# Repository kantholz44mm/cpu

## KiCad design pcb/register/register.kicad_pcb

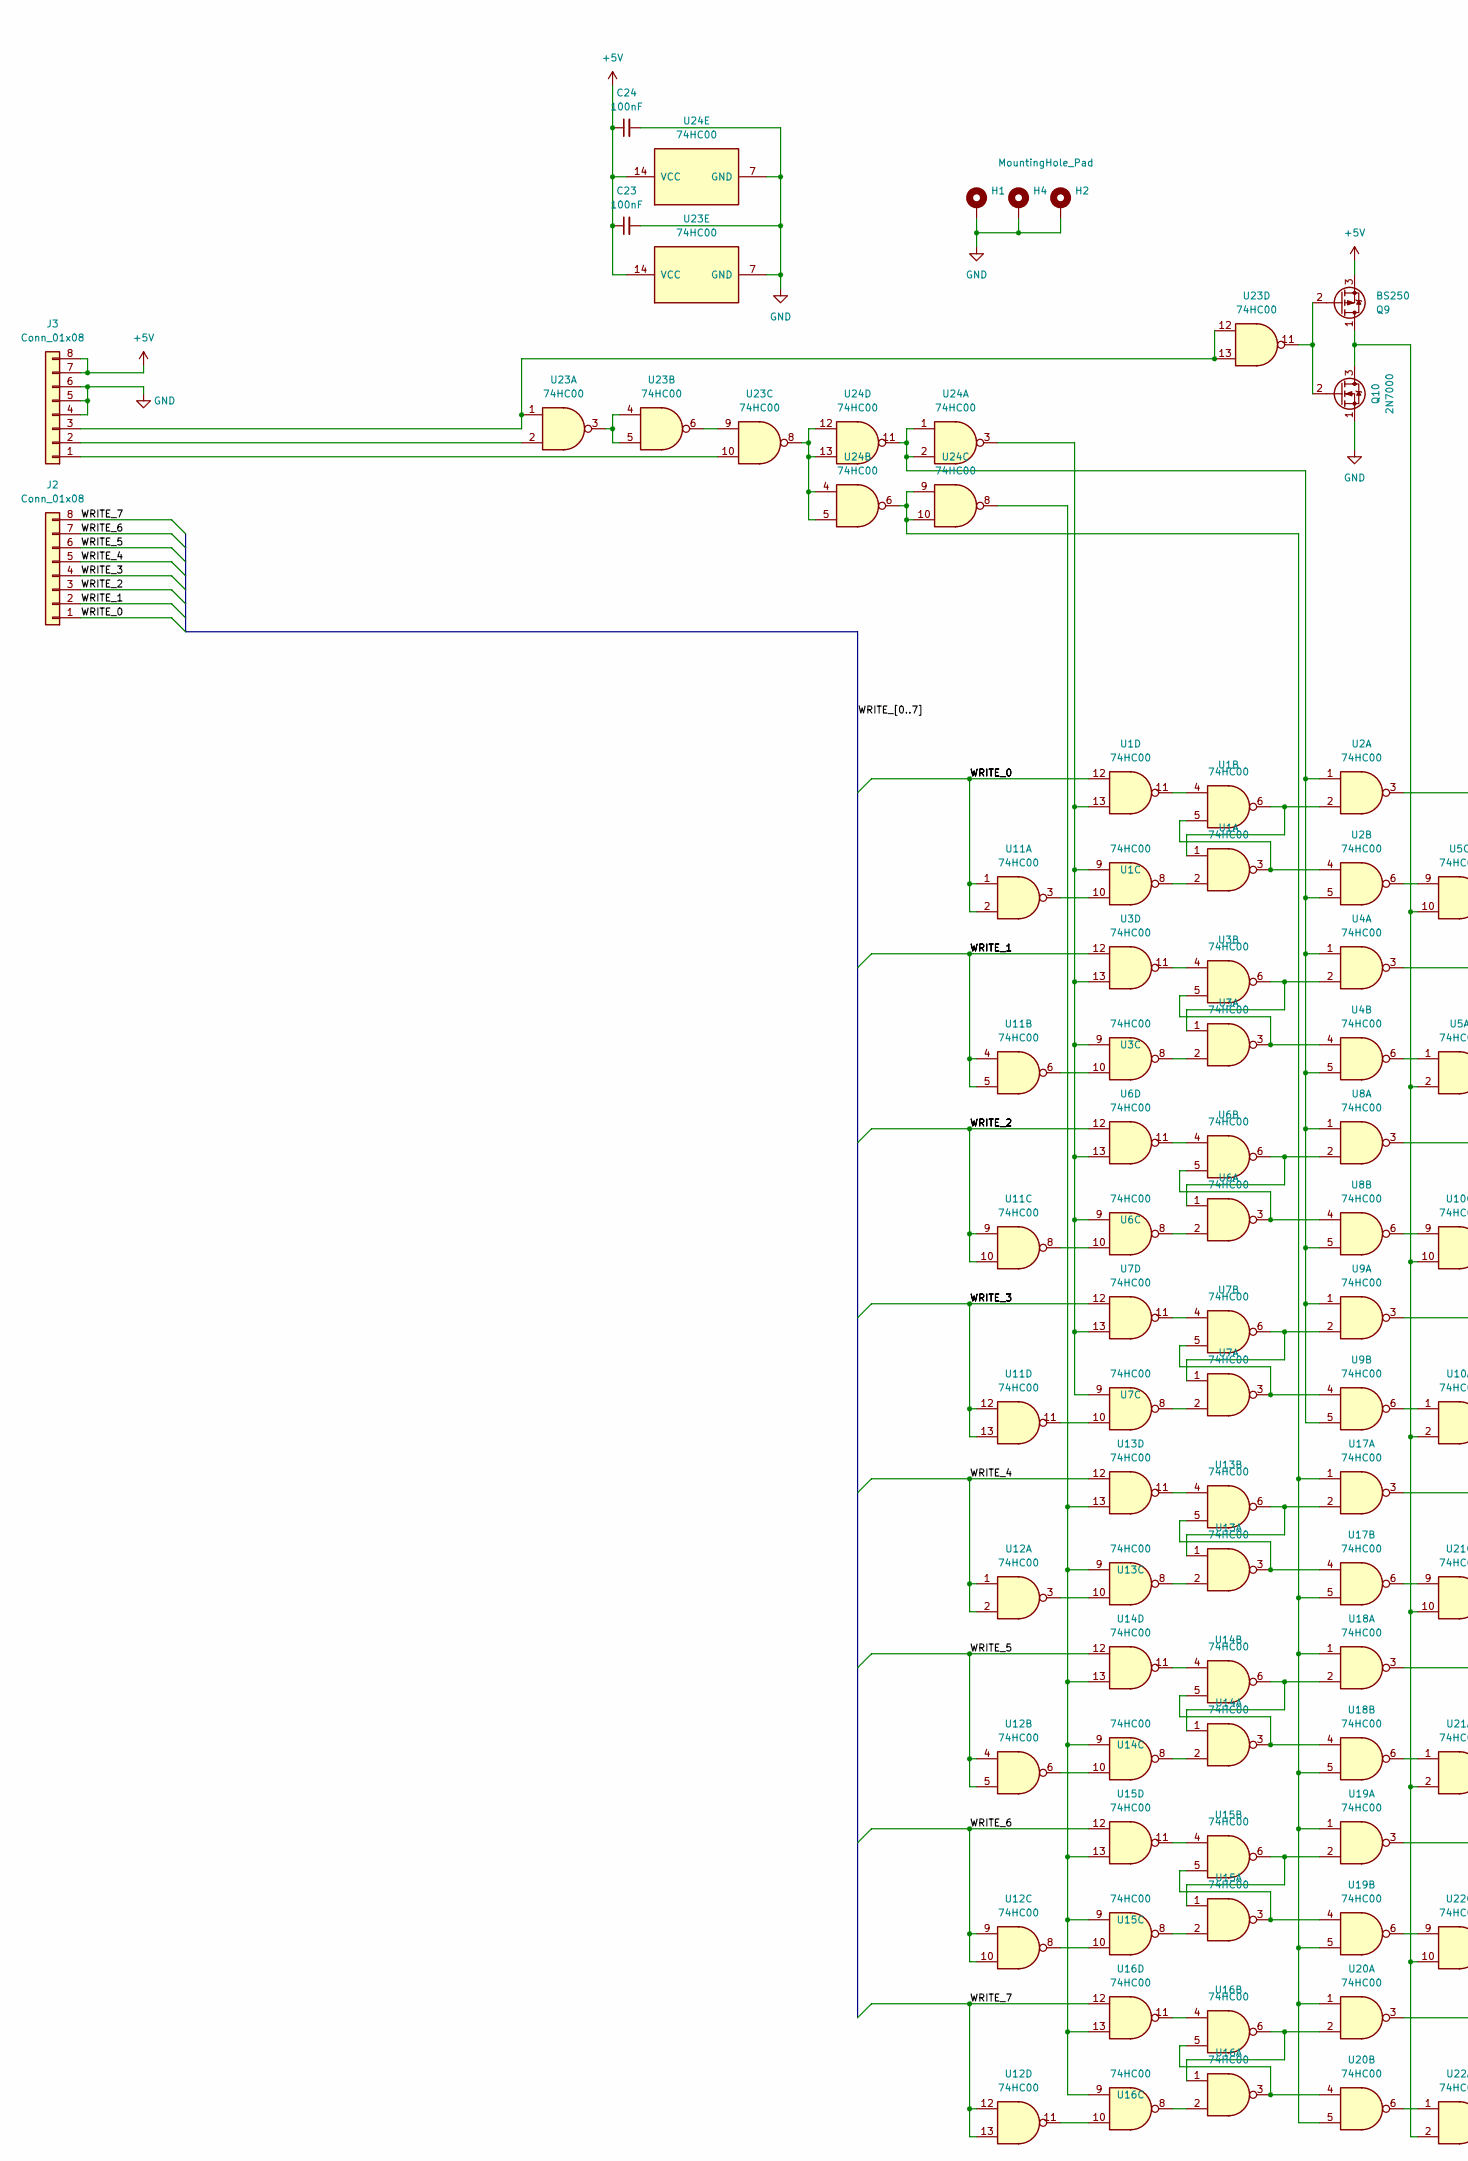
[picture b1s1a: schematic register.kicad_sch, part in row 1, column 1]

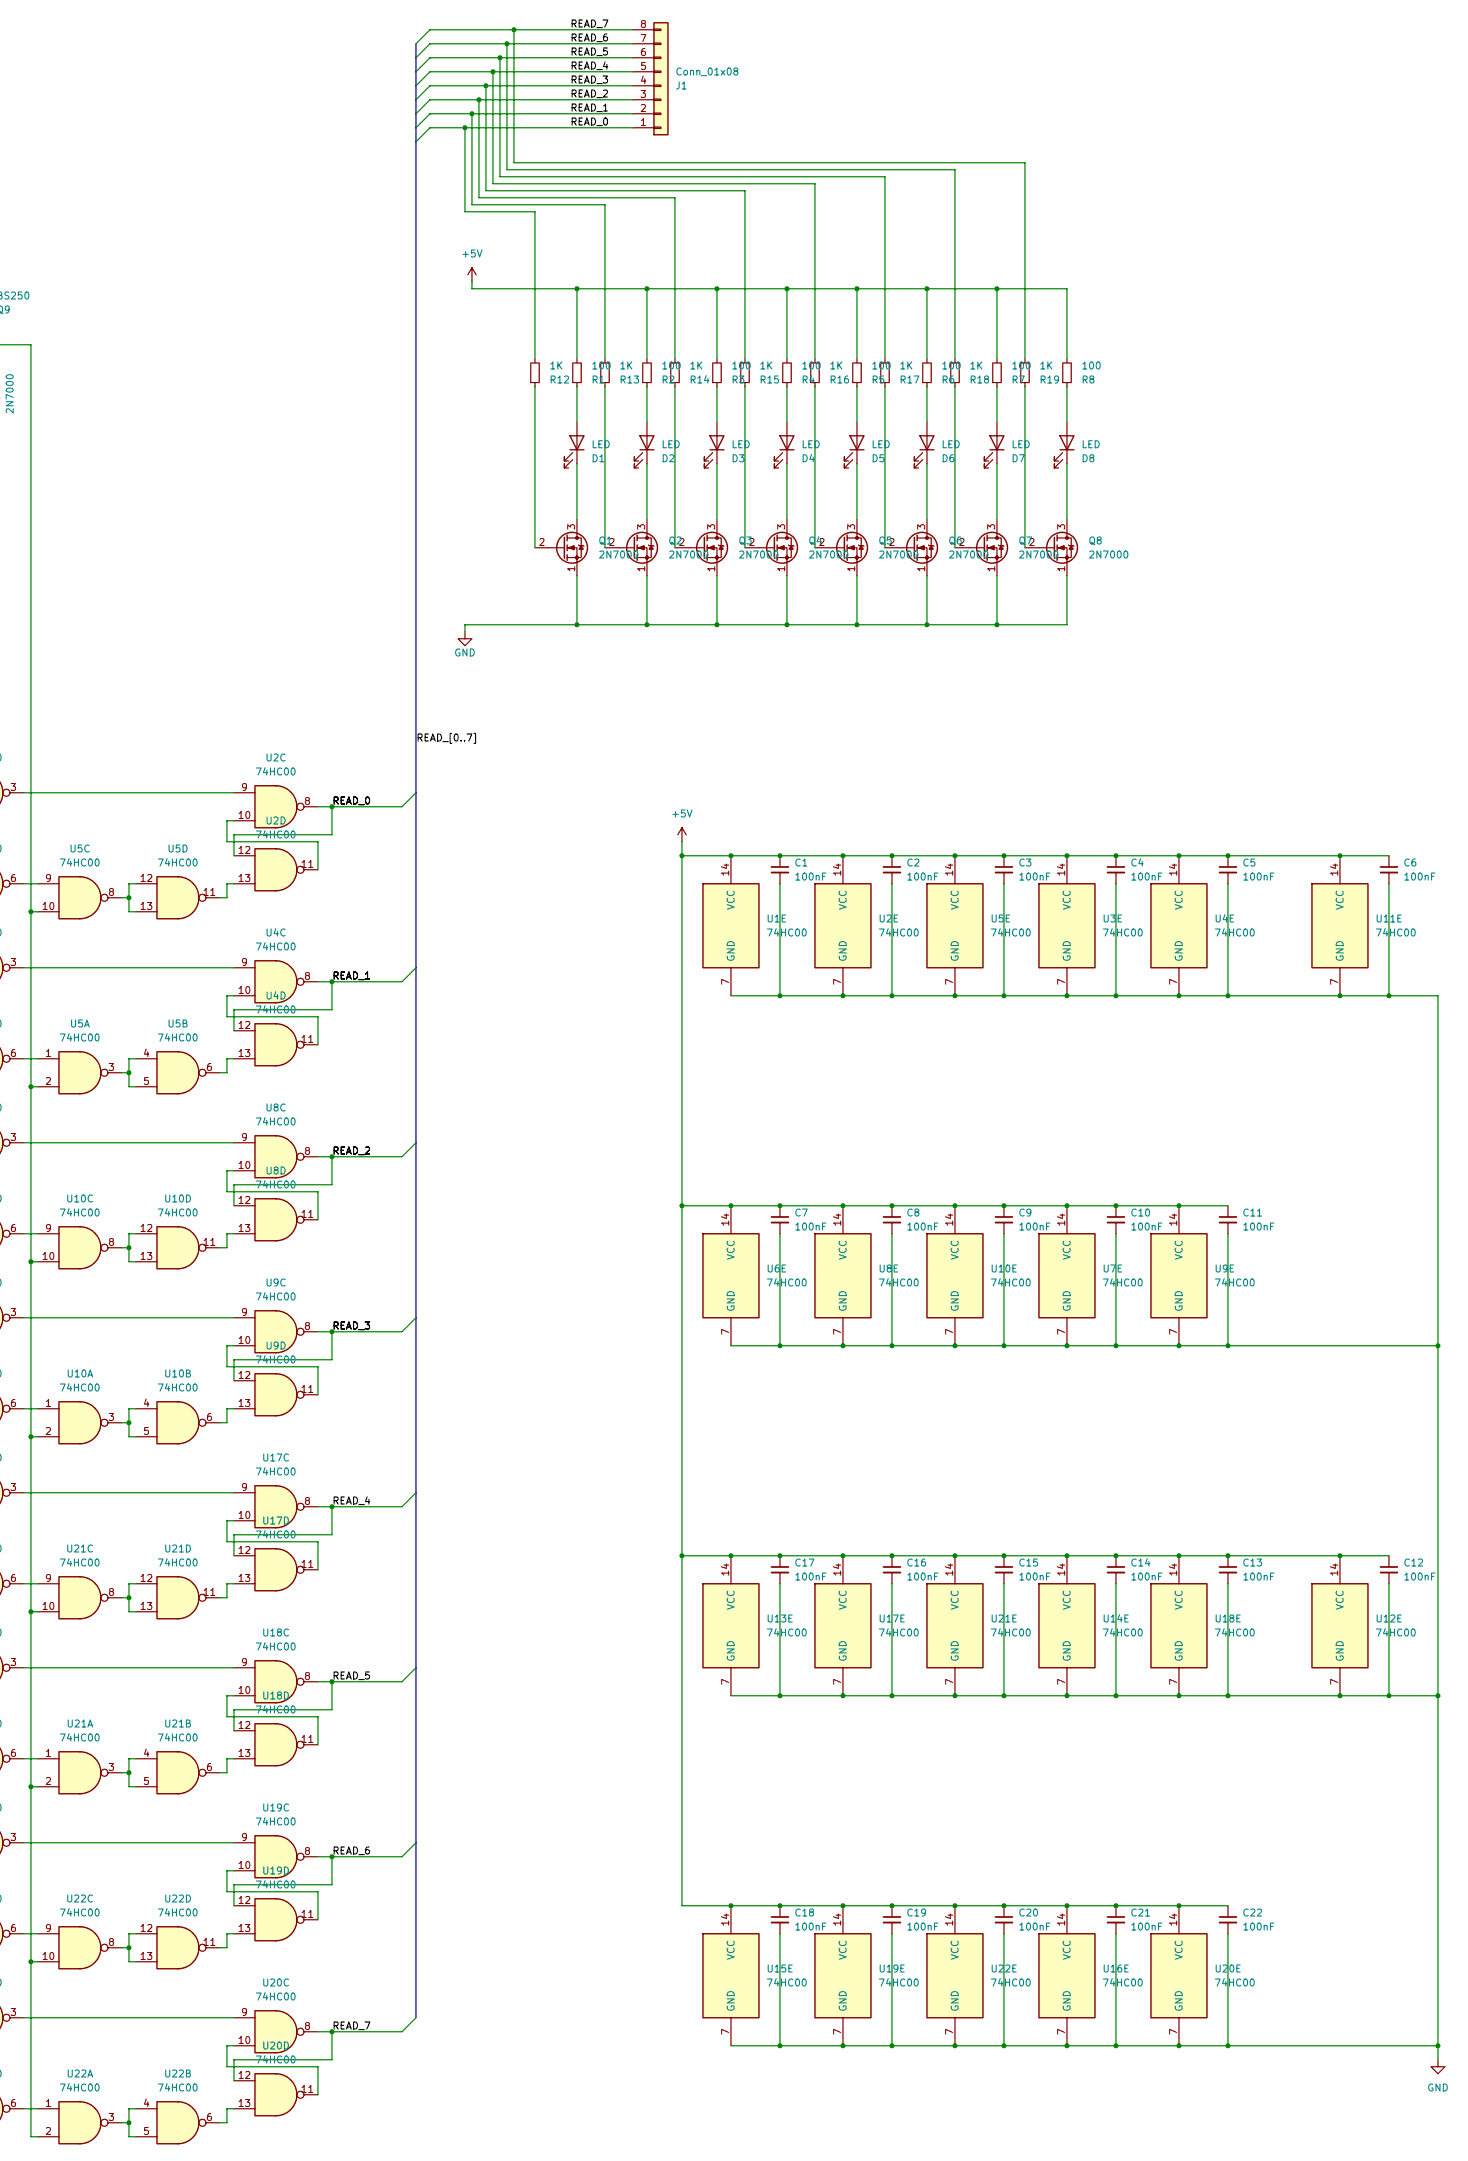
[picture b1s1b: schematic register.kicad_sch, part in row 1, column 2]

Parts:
C1, C2, C3, C4, C5, C6, C7, C8, C9, C10, C11, C12, C13, C14, C15, C16, C17, C18, C19, C20, C21, C22, C23, C24: 100nF; C_Radial_D5.0mm_H11.0mm_P2.00mm
D1, D2, D3, D4, D5, D6, D7, D8: LED; LED_D3.0mm
H1, H2, H4: MountingHole_Pad; MountingHole_3.5mm_Pad
J1, J2, J3: Conn_01x08; IDC-Header_2x04_P2.54mm_Vertical
Q1, Q2, Q3, Q4, Q5, Q6, Q7, Q8, Q10: 2N7000; TO-92_Inline
Q9: BS250; TO-92_Inline
R1, R2, R3, R4, R5, R6, R7, R8: 100; R_Axial_DIN0207_L6.3mm_D2.5mm_P7.62mm_Horizontal
R12, R13, R14, R15, R16, R17, R18, R19: 1K; R_Axial_DIN0207_L6.3mm_D2.5mm_P7.62mm_Horizontal
U1, U2, U3, U4, U5, U6, U7, U8, U9, U10, U11, U12, U13, U14, U15, U16, U17, U18, U19, U20, U21, U22, U23, U24: 74HC00; DIP-14_W7.62mm_LongPads

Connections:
+5V: C1.1, C2.1, C3.1, C4.1, C5.1, C6.1, C7.1, C8.1, C9.1, C10.1, C11.1, C12.1, C13.1, C14.1, C15.1, C16.1, C17.1, C18.1, C19.1, C20.1, C21.1, C22.1, C23.1, C24.1, J3.7, J3.8, Q9.3 (S), R1.2, R2.2, R3.2, R4.2, R5.2, R6.2, R7.2, R8.2, U1.14 (VCC), U2.14 (VCC), U3.14 (VCC), U4.14 (VCC), U5.14 (VCC), U6.14 (VCC), U7.14 (VCC), U8.14 (VCC), U9.14 (VCC), U10.14 (VCC), U11.14 (VCC), U12.14 (VCC), U13.14 (VCC), U14.14 (VCC), U15.14 (VCC), U16.14 (VCC), U17.14 (VCC), U18.14 (VCC), U19.14 (VCC), U20.14 (VCC), U21.14 (VCC), U22.14 (VCC), U23.14 (VCC), U24.14 (VCC); also elsewhere on the board
/READ_0: J1.1, R12.2, U2.8, U2.12; also elsewhere on the board
/READ_1: J1.2, R13.2, U4.8, U4.12; also elsewhere on the board
/READ_2: J1.3, R14.2, U8.8, U8.12; also elsewhere on the board
/READ_3: J1.4, R15.2, U9.8, U9.12; also elsewhere on the board
/READ_4: J1.5, R16.2, U17.8, U17.12; also elsewhere on the board
/READ_5: J1.6, R17.2, U18.8, U18.12; also elsewhere on the board
/READ_6: J1.7, R18.2, U19.8, U19.12; also elsewhere on the board
/READ_7: J1.8, R19.2, U20.8, U20.12; also elsewhere on the board
/WRITE_0: J2.1, U1.12, U11.1, U11.2; also elsewhere on the board
/WRITE_1: J2.2, U3.12, U11.4, U11.5; also elsewhere on the board
/WRITE_2: J2.3, U6.12, U11.9, U11.10; also elsewhere on the board
/WRITE_3: J2.4, U7.12, U11.12, U11.13; also elsewhere on the board
/WRITE_4: J2.5, U12.1, U12.2, U13.12; also elsewhere on the board
/WRITE_5: J2.6, U12.4, U12.5, U14.12; also elsewhere on the board
/WRITE_6: J2.7, U12.9, U12.10, U15.12; also elsewhere on the board
/WRITE_7: J2.8, U12.12, U12.13, U16.12; also elsewhere on the board
GND: C1.2, C2.2, C3.2, C4.2, C5.2, C6.2, C7.2, C8.2, C9.2, C10.2, C11.2, C12.2, C13.2, C14.2, C15.2, C16.2, C17.2, C18.2, C19.2, C20.2, C21.2, C22.2, C23.2, C24.2, H1.1, H2.1, H4.1, J3.4, J3.5, J3.6, Q1.1 (S), Q2.1 (S), Q3.1 (S), Q4.1 (S), Q5.1 (S), Q6.1 (S), Q7.1 (S), Q8.1 (S), Q10.1 (S), U1.7 (GND), U2.7 (GND), U3.7 (GND), U4.7 (GND), U5.7 (GND), U6.7 (GND), U7.7 (GND), U8.7 (GND), U9.7 (GND), U10.7 (GND), U11.7 (GND), U12.7 (GND), U13.7 (GND), U14.7 (GND), U15.7 (GND), U16.7 (GND), U17.7 (GND), U18.7 (GND), U19.7 (GND), U20.7 (GND), U21.7 (GND), U22.7 (GND), U23.7 (GND), U24.7 (GND); also elsewhere on the board
unnamed: D1.2 (A), R1.1
unnamed: D1.1 (K), Q1.3 (D)
unnamed: D2.2 (A), R2.1
unnamed: D2.1 (K), Q2.3 (D)
unnamed: D3.2 (A), R3.1
unnamed: D3.1 (K), Q3.3 (D)
unnamed: D4.2 (A), R4.1
unnamed: D4.1 (K), Q4.3 (D)
unnamed: D5.2 (A), R5.1
unnamed: D5.1 (K), Q5.3 (D)
unnamed: D6.2 (A), R6.1
unnamed: D6.1 (K), Q6.3 (D)
unnamed: D7.2 (A), R7.1
unnamed: D7.1 (K), Q7.3 (D)
unnamed: D8.2 (A), R8.1
unnamed: D8.1 (K), Q8.3 (D)
unnamed 34: J3.1, U23.10; also elsewhere on the board
unnamed 35: J3.2, U23.2; also elsewhere on the board
unnamed 36: J3.3, U23.1, U23.12, U23.13; also elsewhere on the board
unnamed: Q1.2 (G), R12.1
unnamed: Q2.2 (G), R13.1
unnamed: Q3.2 (G), R14.1
unnamed: Q4.2 (G), R15.1
unnamed: Q5.2 (G), R16.1
unnamed: Q6.2 (G), R17.1
unnamed: Q7.2 (G), R18.1
unnamed: Q8.2 (G), R19.1
unnamed: Q9.1 (D), Q10.3 (D), U5.2, U5.10, U10.2, U10.10, U21.2, U21.10, U22.2, U22.10
unnamed: Q9.2 (G), Q10.2 (G), U23.11
unnamed: U1.1, U1.6, U2.2
unnamed: U1.2, U1.8
unnamed: U1.3, U1.5, U2.4
unnamed: U1.10, U11.3
unnamed: U1.4, U1.11
unnamed: U1.9, U1.13, U3.9, U3.13, U6.9, U6.13, U7.9, U7.13, U24.3
unnamed: U2.1, U2.5, U4.1, U4.5, U8.1, U8.5, U9.1, U9.5, U24.1, U24.2, U24.11
unnamed: U2.3, U2.9
unnamed: U2.6, U5.9
unnamed: U2.10, U2.11
unnamed: U2.13, U5.11
unnamed: U3.1, U3.6, U4.2
unnamed: U3.2, U3.8
unnamed: U3.3, U3.5, U4.4
unnamed: U3.4, U3.11
unnamed: U4.3, U4.9
unnamed: U4.6, U5.1
unnamed: U4.10, U4.11
unnamed: U4.13, U5.6
unnamed: U5.3, U5.4, U5.5
unnamed: U5.8, U5.12, U5.13
unnamed: U6.1, U6.6, U8.2
unnamed: U6.2, U6.8
unnamed: U6.3, U6.5, U8.4
unnamed: U6.4, U6.11
unnamed: U7.1, U7.6, U9.2
unnamed: U7.2, U7.8
unnamed: U7.3, U7.5, U9.4
unnamed: U7.4, U7.11
unnamed: U8.3, U8.9
unnamed: U8.10, U8.11
unnamed: U9.3, U9.9
unnamed: U9.10, U9.11
unnamed: U9.6, U10.1
unnamed: U10.3, U10.4, U10.5
unnamed: U9.13, U10.6
unnamed: U8.6, U10.9
unnamed: U8.13, U10.11
unnamed: U10.8, U10.12, U10.13
unnamed: U3.10, U11.6
unnamed: U6.10, U11.8
unnamed: U7.10, U11.11
unnamed: U12.3, U13.10
unnamed: U12.6, U14.10
unnamed: U12.8, U15.10
unnamed: U12.11, U16.10
unnamed: U13.1, U13.6, U17.2
unnamed: U13.2, U13.8
unnamed: U13.3, U13.5, U17.4
unnamed: U13.4, U13.11
unnamed: U13.9, U13.13, U14.9, U14.13, U15.9, U15.13, U16.9, U16.13, U24.8
unnamed: U14.1, U14.6, U18.2
unnamed: U14.2, U14.8
unnamed: U14.3, U14.5, U18.4
unnamed: U14.4, U14.11
unnamed: U15.1, U15.6, U19.2
unnamed: U15.2, U15.8
unnamed: U15.3, U15.5, U19.4
unnamed: U15.4, U15.11
unnamed: U16.1, U16.6, U20.2
unnamed: U16.2, U16.8
unnamed: U16.3, U16.5, U20.4
unnamed: U16.4, U16.11
unnamed: U17.1, U17.5, U18.1, U18.5, U19.1, U19.5, U20.1, U20.5, U24.6, U24.9, U24.10
unnamed: U17.3, U17.9
unnamed: U17.6, U21.9
unnamed: U17.10, U17.11
unnamed: U17.13, U21.11
unnamed: U18.3, U18.9
unnamed: U18.6, U21.1
unnamed: U18.10, U18.11
unnamed: U18.13, U21.6
unnamed: U19.3, U19.9
unnamed: U19.6, U22.9
unnamed: U19.10, U19.11
unnamed: U19.13, U22.11
unnamed: U20.3, U20.9
unnamed: U20.6, U22.1
unnamed: U20.10, U20.11
unnamed: U20.13, U22.6
unnamed: U21.3, U21.4, U21.5
unnamed: U21.8, U21.12, U21.13
unnamed: U22.3, U22.4, U22.5
unnamed: U22.8, U22.12, U22.13
unnamed: U23.3, U23.4, U23.5
unnamed: U23.6, U23.9
unnamed: U23.8, U24.4, U24.5, U24.12, U24.13

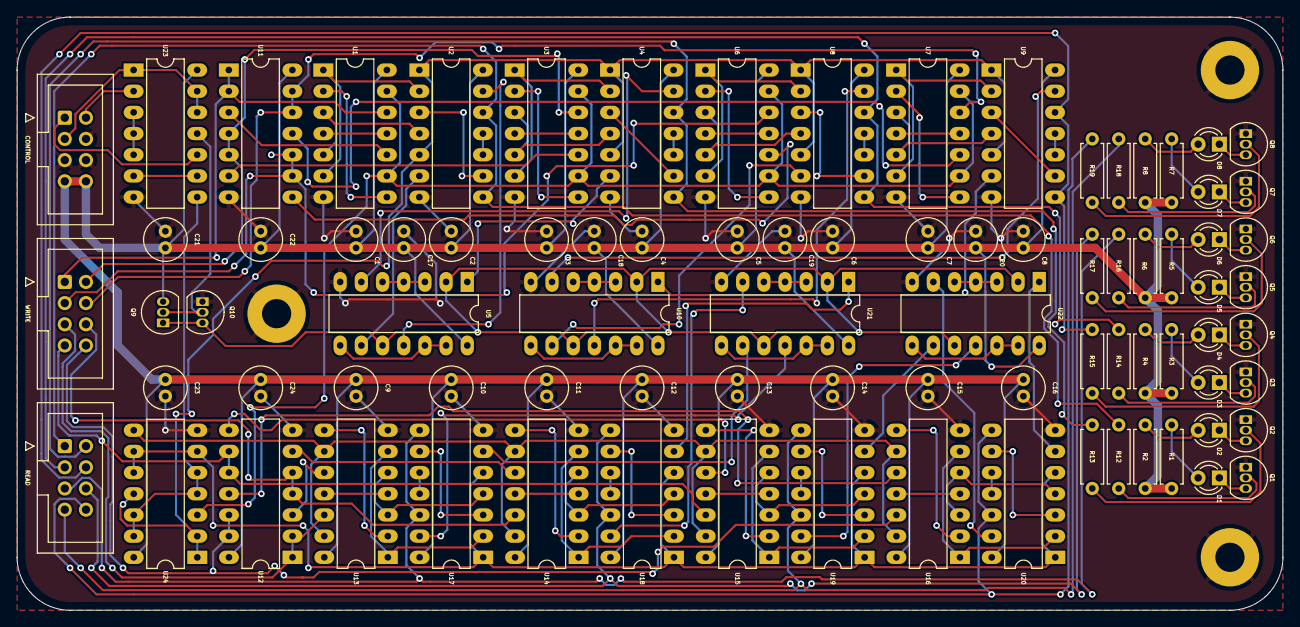
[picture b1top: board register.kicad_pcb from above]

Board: 2 copper layers, 151.8 x 71.1 mm, 88 parts (0 on the bottom side), 134 nets.

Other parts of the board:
CONTROL: Conn_01x08; IDC-Header_2x04_P2.54mm_Vertical
READ: Conn_01x08; IDC-Header_2x04_P2.54mm_Vertical
WRITE: Conn_01x08; IDC-Header_2x04_P2.54mm_Vertical

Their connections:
+5V: CONTROL.7, CONTROL.8; also elsewhere on the board
/READ_0: READ.1; also elsewhere on the board
/READ_1: READ.2; also elsewhere on the board
/READ_2: READ.3; also elsewhere on the board
/READ_3: READ.4; also elsewhere on the board
/READ_4: READ.5; also elsewhere on the board
/READ_5: READ.6; also elsewhere on the board
/READ_6: READ.7; also elsewhere on the board
/READ_7: READ.8; also elsewhere on the board
/WRITE_0: WRITE.1; also elsewhere on the board
/WRITE_1: WRITE.2; also elsewhere on the board
/WRITE_2: WRITE.3; also elsewhere on the board
/WRITE_3: WRITE.4; also elsewhere on the board
/WRITE_4: WRITE.5; also elsewhere on the board
/WRITE_5: WRITE.6; also elsewhere on the board
/WRITE_6: WRITE.7; also elsewhere on the board
/WRITE_7: WRITE.8; also elsewhere on the board
GND: CONTROL.4, CONTROL.5, CONTROL.6; also elsewhere on the board
unnamed 34: CONTROL.1; also elsewhere on the board
unnamed 35: CONTROL.2; also elsewhere on the board
unnamed 36: CONTROL.3; also elsewhere on the board
